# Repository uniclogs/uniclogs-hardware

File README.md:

# University Class Open Ground Station
UniClOGS ground station hardware for both RF and antenna positioning

## OreSat Ground Station Infrastructure

OreSat will utilize two ground stations for this project, a primary station, and a fully-capable secondary station. The primary station is being constructed by the students involved in the project and will be located on the Portland State University Engineering Building. The secondary station is an existing amateur satellite ground station located at a different location for spatial diversity. It can be used to help verify and check out the primary station as construction progresses, and serve as a backup to the primary station. The two stations are identical.

## RF Links

The ground station infrastructure provides two communications functions between the ground and the spacecraft, (1) downlink communications on UHF for the Telemetry Beacons and Command Responses from the spacecraft, (2) uplink communications on L-Band for the Commands to the spacecraft, and (3) downlink communications on S-band for mission payload and camera data.

The UHF component is centered in the 435 to 438 MHz amateur spacecraft service band and utilizes a circular polarized directional Yagi antenna with a RHCP/LHCP polarization sense switch. The L-Band component is centered in the 1260 to 1270 MHz amateur spacecraft service band designated for uplink only, and utilizes a RHCP circular polarized 2x2 helix array. All of this is mounted on an azimuth/elevation antenna positioner. A coax switch connects the UHF antenna to either a Low Noise Amplifier (LNA) for receiving, or a Power Amplifier (PA) for transmitting. The LNA and PA is then connected to a Software Defined Radio (SDR) that provides both UHF RF input and output signals. The L-Band antenna is directly connected to a PA for transmitting only, and then to the same SDR to provide the L Band RF signal.

The S-Band component is centered on 2.4 to 2.43 GHz amateur spacecraft service spectrum. A 0.5 meter parabolic reflector with a RHCP/LHCP feed is mounted on the same antenna positioner as the UHF and L-Band antenna. A coax switch is used to select RHCP or LHCP signal from the feed, is then fed to a bidirectional PA/LNA. The PA/LNA is connected to a ATH9K IEEE 802.11b adapter that provides both the S-Band RF downlink receiver and uplink transmitter signals.

The SDR used for UHF and L-Band is the LimeSDR from LimeMicro, which utilizes GnuRadio for modulation and demodulation. The emission type is GFSK at 50 kb/s, and was chosen for the capability of the Engineering transceiver radio on the spacecraft, an acceptable performance indicated by the link budget, and is somewhat common in the amateur satellite community.

## Antenna positioner

An antenna positioner controller is used to aim the antenna array and is interfaced serially using the EasyComm control protocol accessible through the HamLib control library. The positioner controller is based on the Open Source hardware/software project by K3NG, and provides the ability for tracking control through HamLib _rotctld_ both locally using GPredict, or by the SatNOGS Client software which provides interconnectivity to the SatNOGS system over the Internet.

## GnuRadio 

Data is passed into/out of the ground station radio through GnuRadio ModCod blocks and can provide raw IQ sample files from the payload data. Doppler shift can be compensated for in real time using the tracking software and an XML/RPC server in GnuRadio.

## Data

The Engineering Control/Telemetry subsystem provides telemetry data to the ground in two forms, a GFSK modulated data frame in response to a command request, and a very short Morse code (CW) modulated telemetry sequence and satellite ID if no activity is present for a given period of time. This Morse code ID allows the satellite to be heard by the general amateur radio community and will help with identifying the satellite once on orbit. There are several satellite housekeeping commands that can be sent up from the ground to control power, attitude and payload functions, and most importantly a command to reliably shut off all RF transmissions if required. All commands up to the satellite are authenticated for security.

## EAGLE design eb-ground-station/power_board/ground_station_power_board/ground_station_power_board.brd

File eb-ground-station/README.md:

## EB ground station subsystems

Subsystems pertaining to the Engineering Building "University Class" Open Ground Station (UniClOGS)

Major components

* Structure
* Antennas
* RF systems
* Network
* Power system
* Tracker
* Lightning protection

## BOM for ground station

<!-- [Here is the Bill of Materials so far](https://docs.google.com/spreadsheets/d/1EBKyHZEIYpfHariDGcVJl7H6Yc5BHaDegu6B_IkEdFo/edit#gid=687688620) --->
[Here is the Bill of Materials](https://docs.google.com/spreadsheets/d/1g-H72wh_L9K5FMgDF-K87dqiwulbmqTZjYWP18Jh5gg/edit#gid=1275452567)

The BOM is divided into six sections organizing to some degree what's needed in each phase of the construction.

| Code    | Phase of construction                       |
| ---------- | ----------------------------------------------- | 
| SDR     | Test SDR and GR                             |
| PANEL | Build station panel                            |
| POS     | Build K3NG positioner controller      |
| ANT     | Antenna components and feedline   |
| ROOF  | Roof structures and appurtenances |
| OPER  | Operations equipment                      |

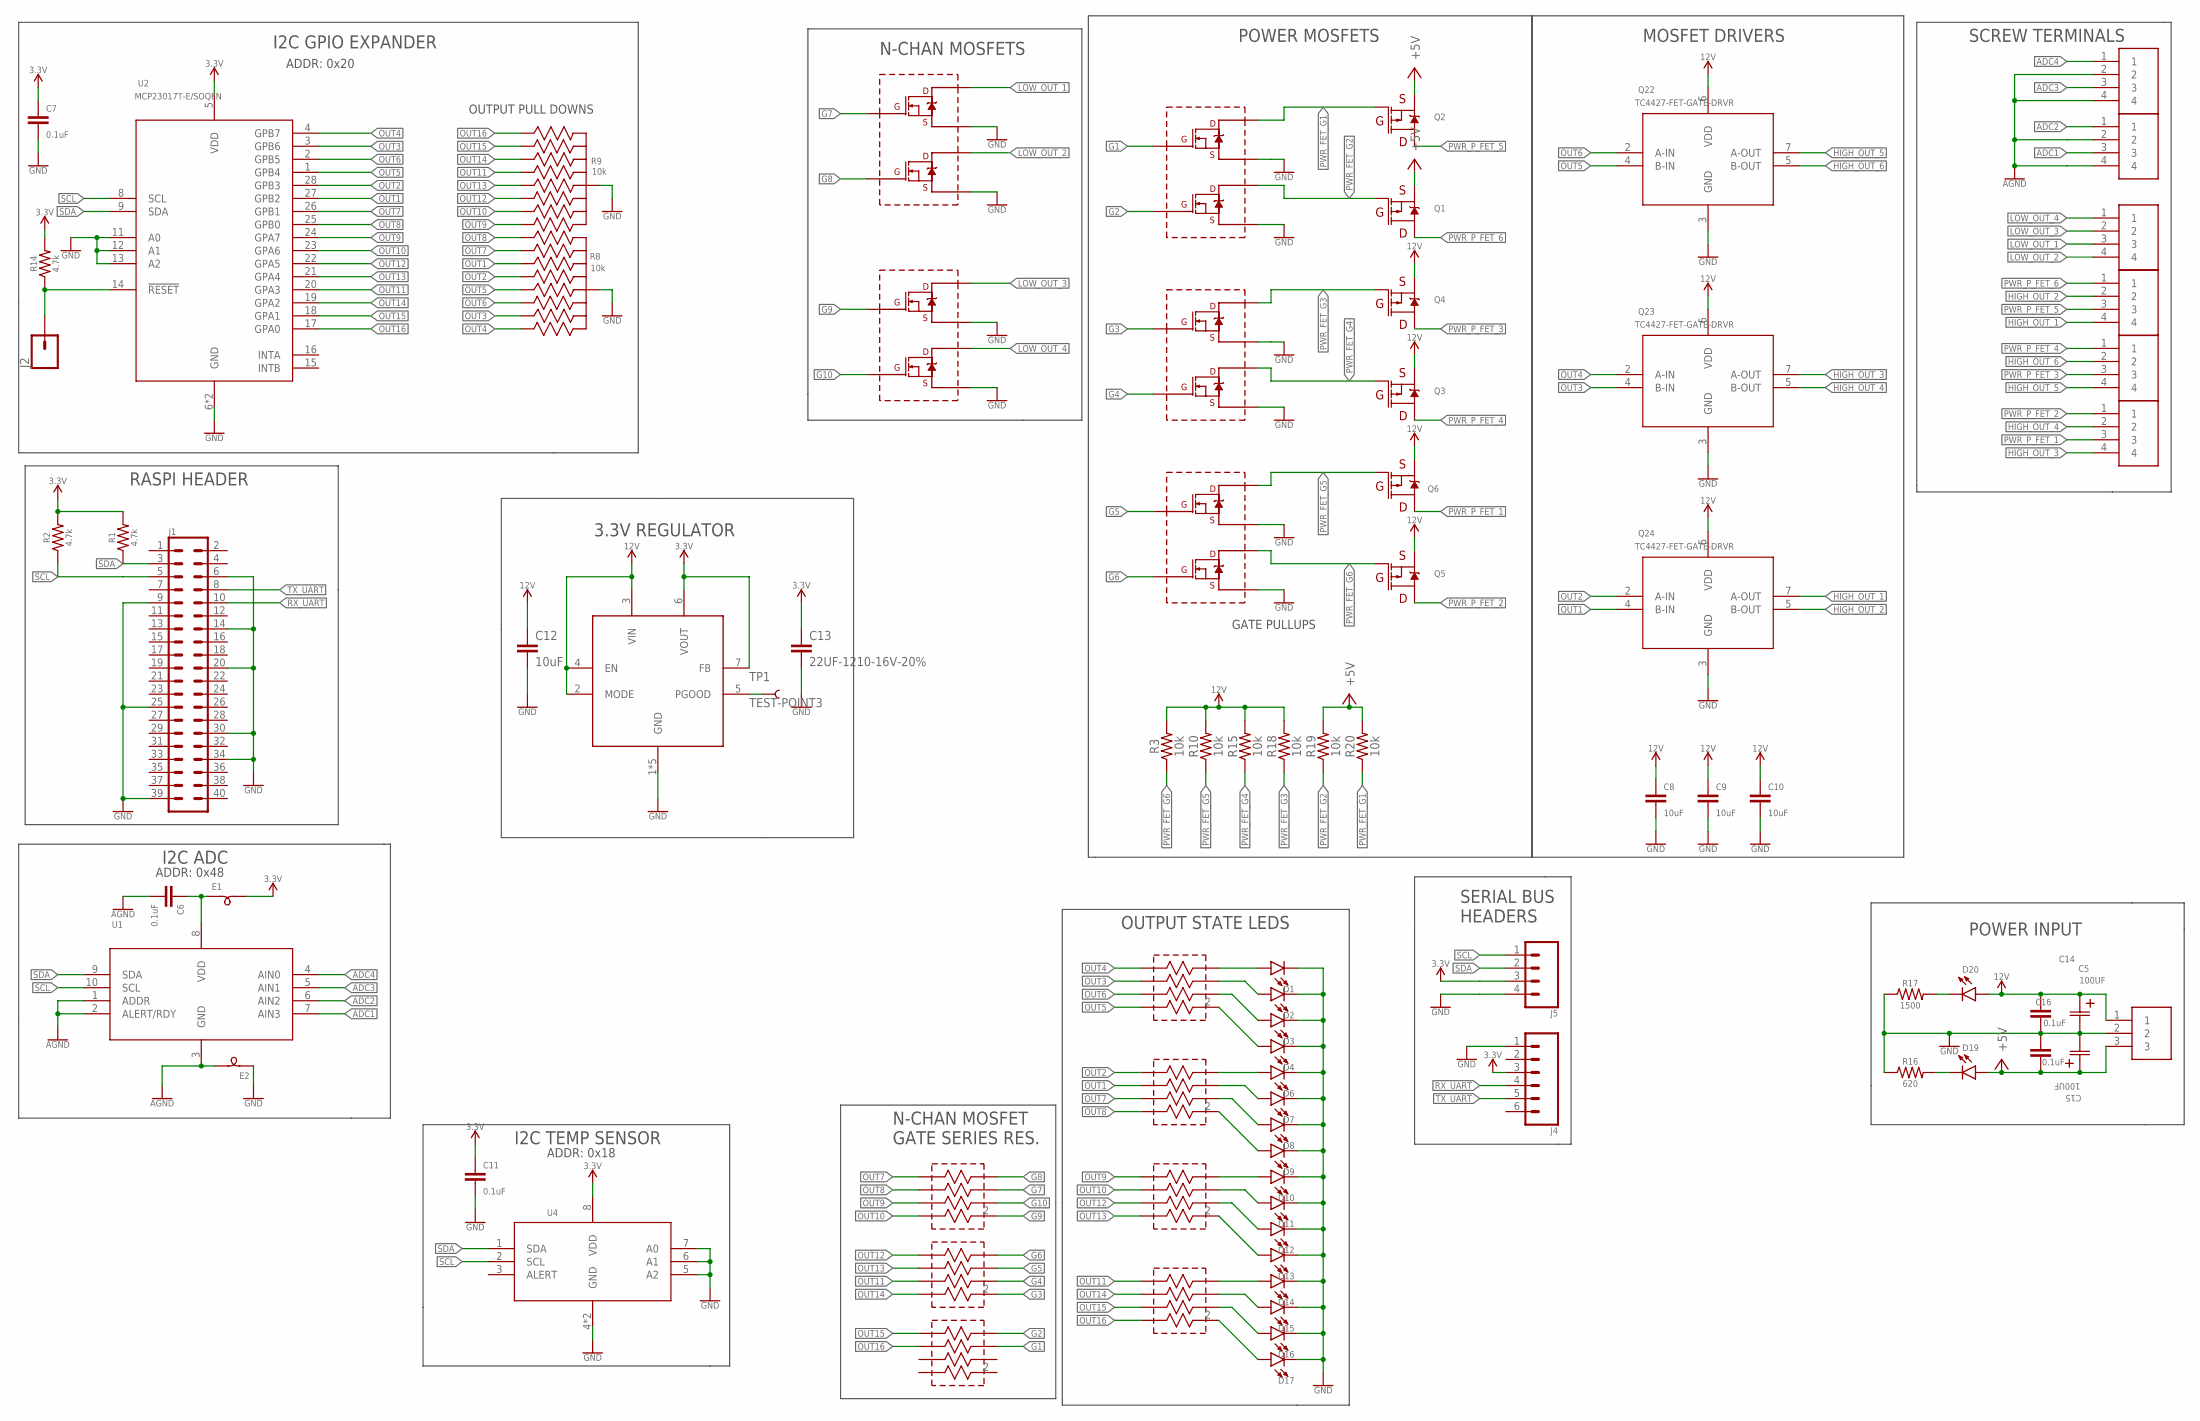
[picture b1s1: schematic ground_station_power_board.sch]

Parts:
C5, C15: 100UF; CHEMI-KE0-M
C6, C7, C11, C14, C16: 0.1uF; 0603
C8, C9, C10: 10uF; 0805
C12: 10uF; 1206
C13: 22UF-1210-16V-20%; 1210
D1, D2, D3, D4, D6, D7, D8, D9, D10, D11, D12, D13, D14, D15, D16, D17, D19, D20: LED0603; LED-0603
E1, E2: L-BEAD-0805-B; .0805-B
J1: CONN_20X2SHROUDED; 2X20_SHROUDED
J2: CONN_01PTH_NO_SILK_KIT; 1X01NS_KIT
J4: CONN_06LONGPADS; 1X06_LONGPADS
J5: CONN_04LONGPADS; 1X04_LONGPADS
Q1, Q2, Q3, Q4, Q5, Q6: SQJ459EP_MOSFET_P_CHAN; POWERPAK_S0-8L
Q8, Q9, Q15, Q17, Q18: DMN61D8LVT-DUAL-N-CHANNEL-MOSFET; TSOT26
Q22, Q23, Q24: TC4427-FET-GATE-DRVR; TSSOP-8
R1, R2, R14: 4.7k; 0603
R3, R10, R15, R18, R19, R20: 10k; 0603
R4, R5, R6, R7: 680; RES-ARRAY-742C083
R8, R9: 10k; C_ARRAY_EXBA-M
R11, R12, R13: 220; RES-ARRAY-742C083
R16: 620; 0603
R17: 1500; 0603
TP1: TEST-POINT3; PAD.03X.03
U1: ADS1115IDGSTDGS10-M; DGS10-M
U2: MCP23017T-E/SOQFN; QFN28_6X6MC-M
U4: MCP9808T-E/MCDFN8_2X3MC-M; DFN8_2X3MC-M
U$1, U$2, U$3, U$4, U$5, U$6: 1719031-PHONEIX-CONTACT-DBL-TERMINAL-BLOCK
U$9: LMZM23601V3SILT; MICRO-SIP
U$11: 1714968-PHONEIX-CONTACT-TERMINAL-BLOCK; 1714968-PHONEIX-CONTACT-3-TERMINAL-BLOCK

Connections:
3.3V: C7.1, C11.1, C13.1, E1.2, J4.3, J5.3, R1.2, R2.2, R14.2, U2.5 (VDD), U4.8 (VDD), U$9.6 (VOUT), U$9.7 (FB)
12V: C5.1 (11), C8.1, C9.1, C10.1, C12.1, C14.1, D20.A, Q3.S1 (S), Q3.S2 (S), Q3.S3 (S), Q4.S1 (S), Q4.S2 (S), Q4.S3 (S), Q5.S1 (S), Q5.S2 (S), Q5.S3 (S), Q6.S1 (S), Q6.S2 (S), Q6.S3 (S), Q22.6 (VDD), Q23.6 (VDD), Q24.6 (VDD), R3.2, R10.2, R15.2, R18.2, U$9.2 (MODE), U$9.3 (VIN), U$9.4 (EN), U$11.1
+5V: C15.1 (11), C16.2, D19.A, Q1.S1 (S), Q1.S2 (S), Q1.S3 (S), Q2.S1 (S), Q2.S2 (S), Q2.S3 (S), R19.2, R20.2, U$11.3
ADC1: U1.7 (AIN3), U$5.3
ADC2: U1.6 (AIN2), U$5.1
ADC3: U1.5 (AIN1), U$6.3
ADC4: U1.4 (AIN0), U$6.1
AGND: C6.2, E2.2, U1.1 (ADDR), U1.2 (ALERT/RDY), U1.3 (GND), U$5.2, U$5.4, U$6.2, U$6.4
G1: Q8.5 (G2), R11.6 (!1OE6)
G2: Q8.2 (G1), R11.8 (!1OE8)
G3: Q9.5 (G2), R12.2 (!1OE2)
G4: Q9.2 (G1), R12.4 (!1OE4)
G5: Q15.5 (G2), R12.6 (!1OE6)
G6: Q15.2 (G1), R12.8 (!1OE8)
G7: Q18.5 (G2), R13.6 (!1OE6)
G8: Q18.2 (G1), R13.8 (!1OE8)
G9: Q17.5 (G2), R13.2 (!1OE2)
G10: Q17.2 (G1), R13.4 (!1OE4)
GND: C5.2 (22), C7.2, C8.2, C9.2, C10.2, C11.2, C12.2, C13.2, C14.2, C15.2 (22), C16.1, D1.C, D2.C, D3.C, D4.C, D6.C, D7.C, D8.C, D9.C, D10.C, D11.C, D12.C, D13.C, D14.C, D15.C, D16.C, D17.C, E2.1, J1.6, J1.9, J1.14, J1.20, J1.25, J1.30, J1.34, J1.39, J4.1, J5.4, Q8.1 (S1), Q8.4 (S2), Q9.1 (S1), Q9.4 (S2), Q15.1 (S1), Q15.4 (S2), Q17.1 (S1), Q17.4 (S2), Q18.1 (S1), Q18.4 (S2), Q22.3 (GND), Q23.3 (GND), Q24.3 (GND), R8.5 (55), R8.10 (55), R9.5 (55), R9.10 (55), R16.1, R17.1, U2.6 (GND), U2.11 (A0), U2.12 (A1), U2.13 (A2), U2.29 (GND), U4.4 (GND), U4.5 (A2), U4.6 (A1), U4.7 (A0), U4.9 (GND), U$9.1 (GND), U$9.TP (GND), U$9.V1 (GND), U$9.V2 (GND), U$9.V3 (GND), U$11.2
HIGH_OUT_1: Q24.7 (A-OUT), U$3.4
HIGH_OUT_2: Q24.5 (B-OUT), U$3.2
HIGH_OUT_3: Q23.7 (A-OUT), U$1.4
HIGH_OUT_4: Q23.5 (B-OUT), U$1.2
HIGH_OUT_5: Q22.7 (A-OUT), U$2.4
HIGH_OUT_6: Q22.5 (B-OUT), U$2.2
LOW_OUT_1: Q18.3 (D2), U$4.3
LOW_OUT_2: Q18.6 (D1), U$4.4
LOW_OUT_3: Q17.3 (D2), U$4.2
LOW_OUT_4: Q17.6 (D1), U$4.1
unnamed: D1.A, R4.8 (!1OE8)
unnamed: D2.A, R4.6 (!1OE6)
unnamed: D3.A, R4.4 (!1OE4)
unnamed: D4.A, R4.2 (!1OE2)
unnamed: C6.1, E1.1, U1.8 (VDD)
unnamed: J2.1, R14.1, U2.14 (!RESET)
unnamed: TP1.P$1, U$9.5 (PGOOD)
unnamed: D19.C, R16.2
unnamed: D6.A, R5.8 (!1OE8)
unnamed: D7.A, R5.6 (!1OE6)
unnamed: D8.A, R5.4 (!1OE4)
unnamed: D9.A, R5.2 (!1OE2)
unnamed: D20.C, R17.2
unnamed: D10.A, R6.8 (!1OE8)
unnamed: D11.A, R6.6 (!1OE6)
unnamed: D12.A, R6.4 (!1OE4)
unnamed: D13.A, R6.2 (!1OE2)
unnamed: D14.A, R7.8 (!1OE8)
unnamed: D15.A, R7.6 (!1OE6)
unnamed: D16.A, R7.4 (!1OE4)
unnamed: D17.A, R7.2 (!1OE2)
OUT1: Q24.4 (B-IN), R5.5 (!1OE5), R8.2 (22), U2.27 (GPB2)
OUT2: Q24.2 (A-IN), R5.7 (!1OE7), R8.8 (88), U2.28 (GPB3)
OUT3: Q23.4 (B-IN), R4.5 (!1OE5), R8.4 (44), U2.3 (GPB6)
OUT4: Q23.2 (A-IN), R4.7 (!1OE7), R8.6 (66), U2.4 (GPB7)
OUT5: Q22.4 (B-IN), R4.1 (!1OE1), R8.3 (33), U2.1 (GPB4)
OUT6: Q22.2 (A-IN), R4.3 (!1OE3), R8.7 (77), U2.2 (GPB5)
OUT7: R5.3 (!1OE3), R8.9 (99), R13.7 (!1OE7), U2.26 (GPB1)
OUT8: R5.1 (!1OE1), R8.1 (11), R13.5 (!1OE5), U2.25 (GPB0)
OUT9: R6.7 (!1OE7), R9.6 (66), R13.3 (!1OE3), U2.24 (GPA7)
OUT10: R6.5 (!1OE5), R9.4 (44), R13.1 (!1OE1), U2.23 (GPA6)
OUT11: R7.7 (!1OE7), R9.8 (88), R12.3 (!1OE3), U2.20 (GPA3)
OUT12: R6.3 (!1OE3), R9.7 (77), R12.7 (!1OE7), U2.22 (GPA5)
OUT13: R6.1 (!1OE1), R9.3 (33), R12.5 (!1OE5), U2.21 (GPA4)
OUT14: R7.5 (!1OE5), R9.2 (22), R12.1 (!1OE1), U2.19 (GPA2)
OUT15: R7.3 (!1OE3), R9.9 (99), R11.7 (!1OE7), U2.18 (GPA1)
OUT16: R7.1 (!1OE1), R9.1 (11), R11.5 (!1OE5), U2.17 (GPA0)
PWR_FET_G1: Q2.G, Q8.3 (D2), R20.1
PWR_FET_G2: Q1.G, Q8.6 (D1), R19.1
PWR_FET_G3: Q4.G, Q9.3 (D2), R18.1
PWR_FET_G4: Q3.G, Q9.6 (D1), R15.1
PWR_FET_G5: Q6.G, Q15.3 (D2), R10.1
PWR_FET_G6: Q5.G, Q15.6 (D1), R3.1
PWR_P_FET_1: Q6.D1 (D), U$1.3
PWR_P_FET_2: Q5.D1 (D), U$1.1
PWR_P_FET_3: Q4.D1 (D), U$2.3
PWR_P_FET_4: Q3.D1 (D), U$2.1
PWR_P_FET_5: Q2.D1 (D), U$3.3
PWR_P_FET_6: Q1.D1 (D), U$3.1
RX_UART: J1.10, J4.4
SCL: J1.5, J5.1, R2.1, U1.10 (SCL), U2.8 (SCL), U4.2 (SCL)
SDA: J1.3, J5.2, R1.1, U1.9 (SDA), U2.9 (SDA), U4.1 (SDA)
TX_UART: J1.8, J4.5

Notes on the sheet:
SCREW TERMINALS
MOSFET DRIVERS
N-CHAN MOSFET GATE SERIES RES.
POWER MOSFETS
N-CHAN MOSFETS
GATE PULLUPS
OUTPUT PULL DOWNS
SERIAL BUS HEADERS
I2C GPIO EXPANDER
OUTPUT STATE LEDS
RASPI HEADER
I2C TEMP SENSOR
I2C ADC
ADDR: 0x20
ADDR: 0x48
ADDR: 0x18
3.3V REGULATOR
POWER INPUT

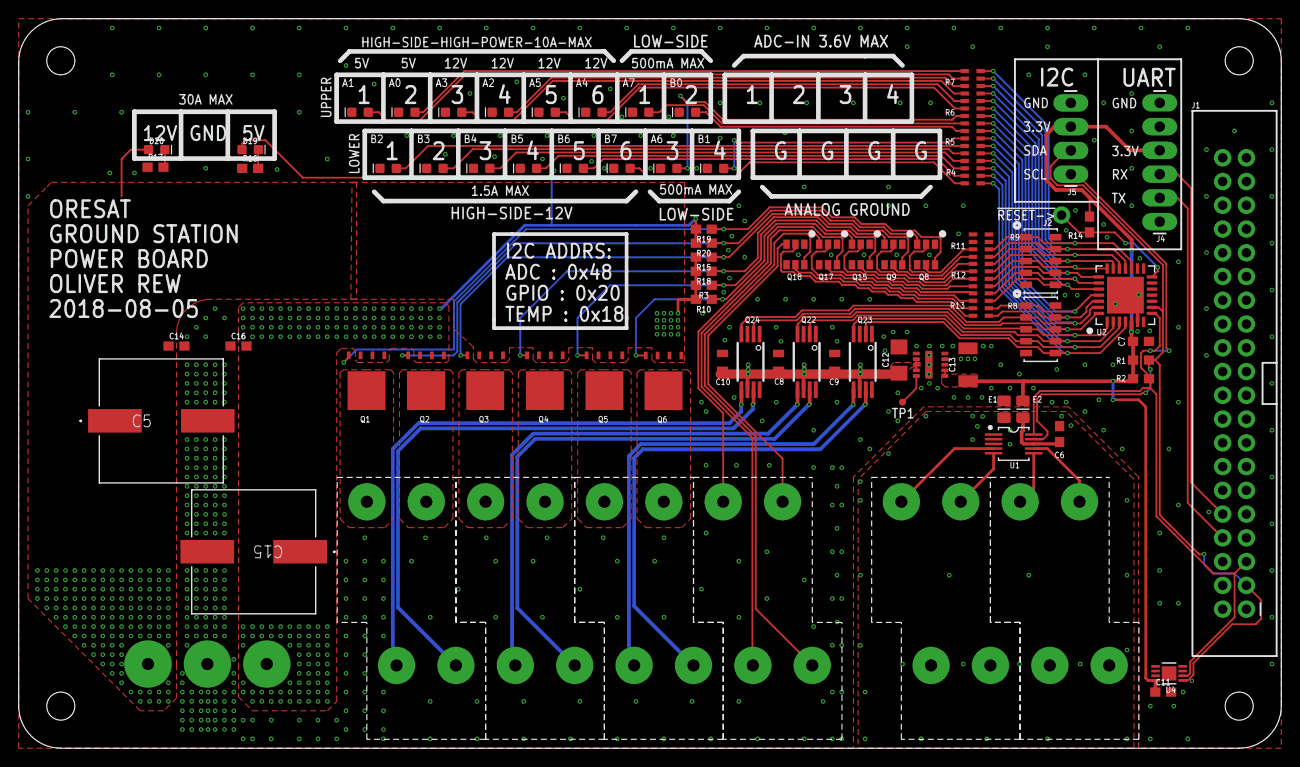
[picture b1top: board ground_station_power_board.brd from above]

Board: 2 copper layers, 135.0 x 78.0 mm, 83 parts (1 on the bottom side), 82 nets.

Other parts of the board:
U$8: PSAS_LOGO_15X15

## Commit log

2017-08-10 Update README.md
    Put in content that explains the various parts of the primary ground station.
2017-08-10 README update
    Separated contents by function, added project team members.
2017-08-11 Update README
    Setup the doc sub directory
2017-08-11 Update README
    Setup the SatNOGS ground station sub directory
2017-08-11 Create eb-ground-station
    Setup EB ground station sub directory
2017-08-11 Delete eb-ground-station
    Woops I made a mistake!
2017-08-11 Create README.md
    Setup the EB ground station sub directory, and README
2017-08-11 Create README.md
    Created as a markdown as I should have the first time.
2017-08-11 Create README.md
    Created as a markdown file as I should have the first time.
2017-08-11 Update README.md
    Give a little insight as to what is in the sub directories.
2017-08-11 Upload block diagram of the EB station GS_3_4.pdf
    This PDF was created using Visio.
2017-08-11 Update README.md
    Add the EB Station block diagram
2017-08-11 Upload GS_3_4.png
    PNG used in the README.md
2017-08-11 Update README.md
    Change block
2017-08-12 Updated EB GS block diagram to GS_3_5, and added structural drawing for augmented mast. Also updated main README.md
2017-08-12 Woops, forgot to place the GS block diagram into the docs directory. Also deleted the old version of the block diagram.
2017-08-14 Added site photos and drawings
2017-08-14 Update README.md
    Said words about the photos and hand drawings
2017-08-17 Added document describing augmented ground station requirements
2017-08-17 Fixed some of the wording in the requirements document
2017-08-18 I did a first order approximation of the rooftop ground station in solidworks using Glenn's wind loading numbers.
2017-08-18 organized my mess
2017-09-01 started a notebook on wind loading
2017-09-05 Added Mark M's photos of testing SatNOGS helix antenna in satnogs directory
2017-09-06 Update notes.md
    Some updates to notes.md describing photos, and VNA marker frequency.
2017-09-07 added organization & resources to the notebook
2017-09-08 more ancillary stuff to the GS notebook
2017-09-09 Added Jeremy's notes for computing ballast mass
2017-09-10 added more unit conversions
2017-09-10 uniiiiiiiiiiiitttttttttsssss!!!
2017-09-11 switched to using the magnitude package for units
2017-09-14 Reorganized directory making subsystem directories, and pulled some of the larger issues into the README for that subsystem
2017-09-14 Reorganized for independent structure, and augmented weather station. Also included component cut-sheets, and TIA documents
2017-09-17 more book-keeping of drag-y mass-y stuff
2017-09-17 finished calculations; TODO: confirm input params
2017-09-21 shear and bending on the ground station mast
    TODO:
    * comment the code, so I will know what it does a week from now.
    * I suppose I'm also neglecting the fact that the legs have a reaction
    in the -Z direction, which compresses the mast. That's definitely not
    negligible. I should account for that.
    * change the structure of the notebook to be intro -> tipping -> bending
2017-09-23 initial calculations for the independent EBGS
    These were used in my conversation with Glenn to guide part selection
    for the ground station.
    I just coppied over the analysis from the tripod weather station,
    setting stuff like the leg diameters to zero to adapt the calculations
    to work for a stand-alone base plate.
    I would like to go back and pretty-up the notebook so that the variable
2017-09-29 Update README.md
    Update BOM to v1.2
2017-09-29 Update README.md
    Move BOM to main README
2017-09-29 Update README.md
    Change organisation of RF Systems README
2017-09-29 cleaned up the names in the EBGS 1.2 notebook
2017-10-03 Roof layout drawing; Rohn mast info and quote; Annotated roof view
2017-10-05 Updated site drwaing for structure, organized directory contents, included quote for mast frame.
2017-10-05 Upload some stuff that seems to have been left out?
2017-10-05 Uploaded SatNOGS Arduino Controller code provided by MarkM for reference
2017-10-15 Updated site layout drawing closer to conduit, and added simple narrative document
2017-12-11 Marked location of equipment enclosure and moved walkway to accommodate
2017-12-11 Include the Visio file for the updated groundstation drawing
2018-01-28 Add files via upload
    Got the shcematic!
2018-01-28 Add files via upload
    schematic!
2018-01-28 Added controller files
2018-01-28 ReadMe for controller
    Link to Osh Park PCB site
2018-02-12 Add Gitter badge
2018-07-07 Simple tool for converting decimal inches to fractional inches. (1/16 resolution)
2018-07-23 Started the ground station power board
2018-07-26 progress on the power board
2018-07-28 Power board is mostly wrapped up
2018-07-31 some final changes
2018-07-31 prettied up the schematic
2018-07-31 deleted files
2018-07-31 Approved ERC and DRC
2018-07-31 added vias
2018-07-31 I can't stop making changes HELP!
2018-08-01 every time I look at this I add 40 more vias
2018-08-03 added decoupling cap and some labels
2018-08-03 added SMPS
2018-08-05 Add board function document and software state diagram
2018-08-06 Updated for 2 5V mosfets
2018-08-06 small fixes
2018-08-06 moved some silk
2018-08-06 moved via
2018-08-06 label change
2018-08-06 fixed logo
2018-08-21 Initial addition of Chad's state machine from ACS.x
2018-08-21 Tabs to spaces because I'm a basic bitch
2018-08-21 Missed one
2018-08-23 Add names and some transition functions
2018-08-24 i2c initial commit
2018-08-25 L Band transition left
2018-08-26 Add state transitions
2018-08-27 add transitions
2018-08-29 working i2c on raspberry pi
2018-08-30 rename from ACS to PWR
2018-08-30 Finish renaming the things I missed
2018-08-30 Bug fixing, remembering how text based languages work
2018-09-02 Missed folder name
2018-09-03 Add I2C code, untested
2018-09-05 Initial commit of daemon related code. Beginning option framework
2018-09-06 Implemented forking
2018-09-07 Added usage information.
2018-09-17 First I2C statemachin test, needs clean up.
2018-09-17 Update Station_Board.txt
    Swapped IO points between rotator power and S-Band power.
2018-09-20 deleting temp src files.
2018-10-16 created readme for ground power board.
2018-10-16 initial code
2018-10-19 fixing compilation issues
2018-10-19 correct few compile errors.
2018-10-19 correct to input tokens
2018-10-19 changes to state machine
2018-10-19 added debug message
2018-10-19 changed hardware regs.
2018-10-19 i2c testing
2018-10-21 Update Station_Board.txt
    Move LimeSDR power to high current +12 VDC, and put rotator power relay / Arduino on +5 VDC.
2018-10-21 Photo of wiring diagram
2018-10-21 working i2c
2018-10-21 tested and fixed bugs.
2018-10-23 starting new signal based power code.
2018-10-23 Added MAX_TOKENS on header file.
2018-10-23 handle signals in powerboard.c
2018-10-23 working UNR1 and INT signals.
2018-10-23 Added timer and abort signals. Code tested to be working good.
2018-10-27 Update Station_Board.txt
    Assigned correct GPIO bit numbers to the control outputs.
2018-10-27 Updated gpio pins
2018-11-02 Program variable read instead of chip register reads. Fixed another bug.
2018-11-02 added syslog messages, created a separate make file, added comments.
2018-11-02 some more markdown edits on readme. :)
2019-01-10 Added UniClOGS logo / sticker!
2019-02-11 Renaming as per Andrew's request
2019-03-28 Update README.md
    Add description of L-Band used for uplink channel.
2019-03-28 Add tracker code
2019-03-28 Added directory for current configuration files
2019-03-28 Make the update script work correctly
2019-03-28 Wiring diagrams added
2019-03-29 Organize tracker directory
2019-04-01 Added PA test info, and moved things around
2019-04-01 Updated directory structure
2019-04-01 Restructure more directories and readme updates
2019-05-13 Update to block diagram
2019-05-13 Update README.md
    Fix image name
2019-05-13 Fix file name and place PNG
2019-05-13 Fix text in README
2019-07-13 LTSpice slow start circuit
2019-08-20 "auto-generated from update_repos.py"
2020-12-09 Update README.md
    New BOM Spreadsheet link
2021-03-24 Added latest GS photos
2021-07-24 Added relay driver board design
2021-07-24 Moved some RF relay files to proper place
2021-07-24 Added latching relay driver board kicad files.
2021-07-24 Added BOM for latching relay driver board.
2021-09-15 Photo of completed units
2021-09-15 Added latching relay driver v1.0 gerbers.
2021-09-16 Updated BOM and added design notes txt file
2021-09-16 Update design notes
2021-09-16 Update design notes - 2
2022-04-06 Add pdf of Eagle schematic
2022-04-21 Add UniClOGS RF interconnect document
2022-08-23 New doc; power_buts_1.txt; showing connection between block diagram and state machine.
2022-08-24 Starting V2 in KiCad
2022-08-24 New power board schematic almost done
2022-08-26 First layout done. No slikscreen work yet
2022-08-26 Added PDF schematic
2022-08-27 Added soft start and ground vias
2022-08-27 Fixed some silkscreen
2022-08-27 refdes silkscreen nearly done
2022-08-28 More silkscreen work
2022-08-28 Added PDFs and PNGs of the board
2022-08-29 Added diagrams of the board
2022-08-29 Fixed ~IO_RESET RasPi pin and improved silkscreen
2022-08-29 Fixed some issues and added propper power input connector
2022-08-30 Upgrading Bank A to 16A
2022-09-03 Finished routing with higher current traces
2022-09-04 Silkscreen almost done
2022-09-04 Made new drawings and renders
2022-09-05 Fixed issues discovered during the design review
2022-09-06 Added UART5 breakout pins
2022-09-08 Added BOMs
2022-09-08 Preparing to make changes for unavailable parts
2022-09-19 Fixed silkscreen and switched components
2022-09-19 UPD board is ready for production I think
2022-09-22 Added some documentation
2022-09-23 Fixed small board error
2022-09-23 Added some simulation notes
2022-09-23 Cleaned up the repo
2022-09-25 Changed doc header
2022-10-02 Fixed typo in upd-documentation
2023-01-13 Fixed UPD board, ready for review and ordering
2023-01-15 Fixed pin 1 of expanders being pulldown only
2023-01-15 rev2.1 should be done
2023-01-22 Moved vias out from under test
2023-07-31 modified schematic diagram for clarity
2023-08-17 updated board changes for bom
2025-10-16 Update README.md - PA PreDriver information
    Change information on the Pre-Drivers used in front of the PA sections.
2026-03-01 placed UPD Board configuration files which describe specific stations
2026-03-01 Some things that were laying around since 17-Oct-2025
    This stuff way laying around and somehow did not get pusged.
    :)

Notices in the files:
parts and their libraries:
SparkFun-Connectors: Licensing: Creative Commons ShareAlike 4.0 International - https://creativecommons.org/licenses/by-sa/4.0
